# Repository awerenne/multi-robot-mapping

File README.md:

# Multi-robot environment mapping 

The goal of this project was to construct two robots, able to map unknown environments as quickly as possible. The considered environments are exclusively composed of straight black lines on a white background, intersecting each other with right angles. The robots being only allowed to move along those black lines during the exploration phase.

The developed solution follows a master-slave architecture. Each robot (slave) follows a black line while keeping track of the travelled distance. Once an intersection detected, the robot stops and sends an information message to the master. The message contains the type of intersection encountered and the travelled distance since the previous intersection. This information is then used by a program (master), running locally on a computer, in order to update its internal representation of the environment (i.e. map). The next instruction (stop, straight, turn left or right, uturn) for the robot is then computed and send back to the rboto. This procedure is repeated until the environment is entirely explored.

<p align="center">
    &nbsp;&nbsp;&nbsp;
    
</p>

The left-part of the animation above shows a live screen recording of the master constructing the map, corresponding to the robot exploration performed (displayed in the right-part). A video of the complete demonstration can be found [here](https://www.youtube.com/watch?v=w8zaz-Xr6bw&t=6s). The implementation and results are described in the [report](https://awerenne.github.io/files/pp-report.pdf). The different steps of the construction of the robots are documented [here](https://github.com/awerenne/multi-robot-mapping/blob/master/construction/README.md).

## Simulator
Testing the mapping algorithm with the exploration being performed by physical robots would have been time-consuming. Instead, the exploration was simulated on random environments. 

The algorithm of the master is explained in the [report](report/personal-project.pdf)) (pages 8-11). A simulation can be lauched with <code>python main.py</code> in the folder *code/simulator/*. The flag <code>is_simulation</code> needs to be set to true in the config file.

## Robot
The control of the robot was tested with a simple challenge: following a curved line at a constant speed. To this end, a speed and steering controller were developed (described in the [report](report/personal-project.pdf), pages 20-24). The result is shown in the animation below.

The robot was then further augmented to loop through a serie of steps during the exploration phase. The high-level view of the main algorithm (serie of steps) is implemented in the file *code/robot/mapping/mapping.ino*, which is based on low-level features implemented in the files located in the folder *code/robot/NewCOEX/*. The acronym COEX stands for cooperative explorer. 

## Usage
The simulator can be launched as follows:
1. Set the flag <code>is_simulation</code> to True in the config file.
2. Run the command <code>python main.py</code> (in the folder *code/simulator/*).

The physical exploration can be launched as follows:
1. Copy the folder *code/robot/NewCoex* in your Arduino folder, and load it as a library ([how to load a library](https://www.arduino.cc/en/guide/libraries)).
2. Install the library corresponding to the [QTR-X sensors](https://www.pololu.com/docs/0J19/2).
3. Upload the program *code/robot/mapping/mapping.ino* to the micro-controller.
4. Set the flag <code>is_simulation</code> to False in the config file.
5. Check that the ports in the config files are correctly configured with the names of the bluetooth modules.
5. Switch the power of the robots on and calibrate the line sensors.
6. Run the command <code>python main.py</code> (in the folder *code/master/*).

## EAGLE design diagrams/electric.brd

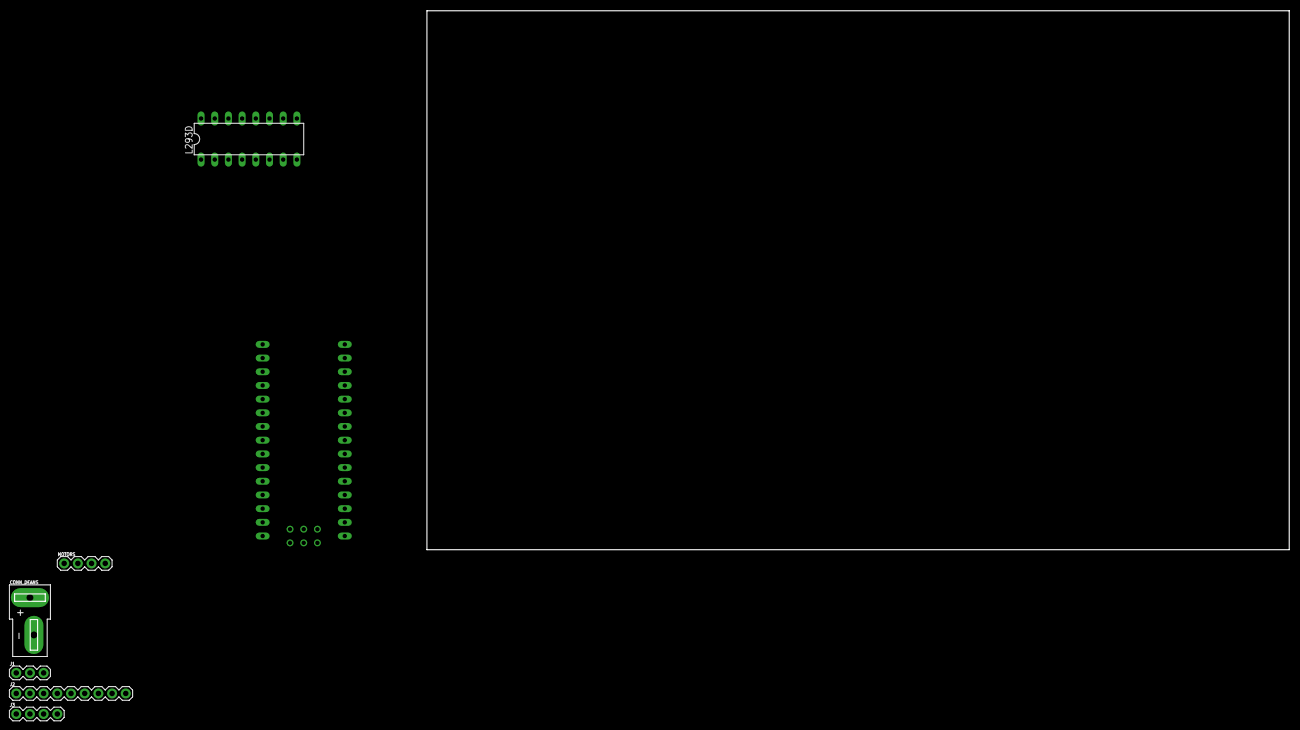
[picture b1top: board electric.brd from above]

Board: 2 copper layers, 7 parts (0 on the bottom side), 7 nets, no tracks yet.

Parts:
CONN_DEANS: DEANS
J1: 1X03
J2: 1X09
J3: 1X04
L293D: L293D; DIL16
MOTORS: 1X04
U$1: NANO

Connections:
GND: CONN_DEANS.-, L293D.4, L293D.5, L293D.12, L293D.13, U$1.GND
GND-LEFT: L293D.6, MOTORS.3
GND-RIGHT: L293D.11, MOTORS.2
V+: CONN_DEANS.+, L293D.8, U$1.RAW
VCC: L293D.16, U$1.5V
VCC-LEFT: L293D.3, MOTORS.4
VCC-RIGHT: L293D.14, MOTORS.1

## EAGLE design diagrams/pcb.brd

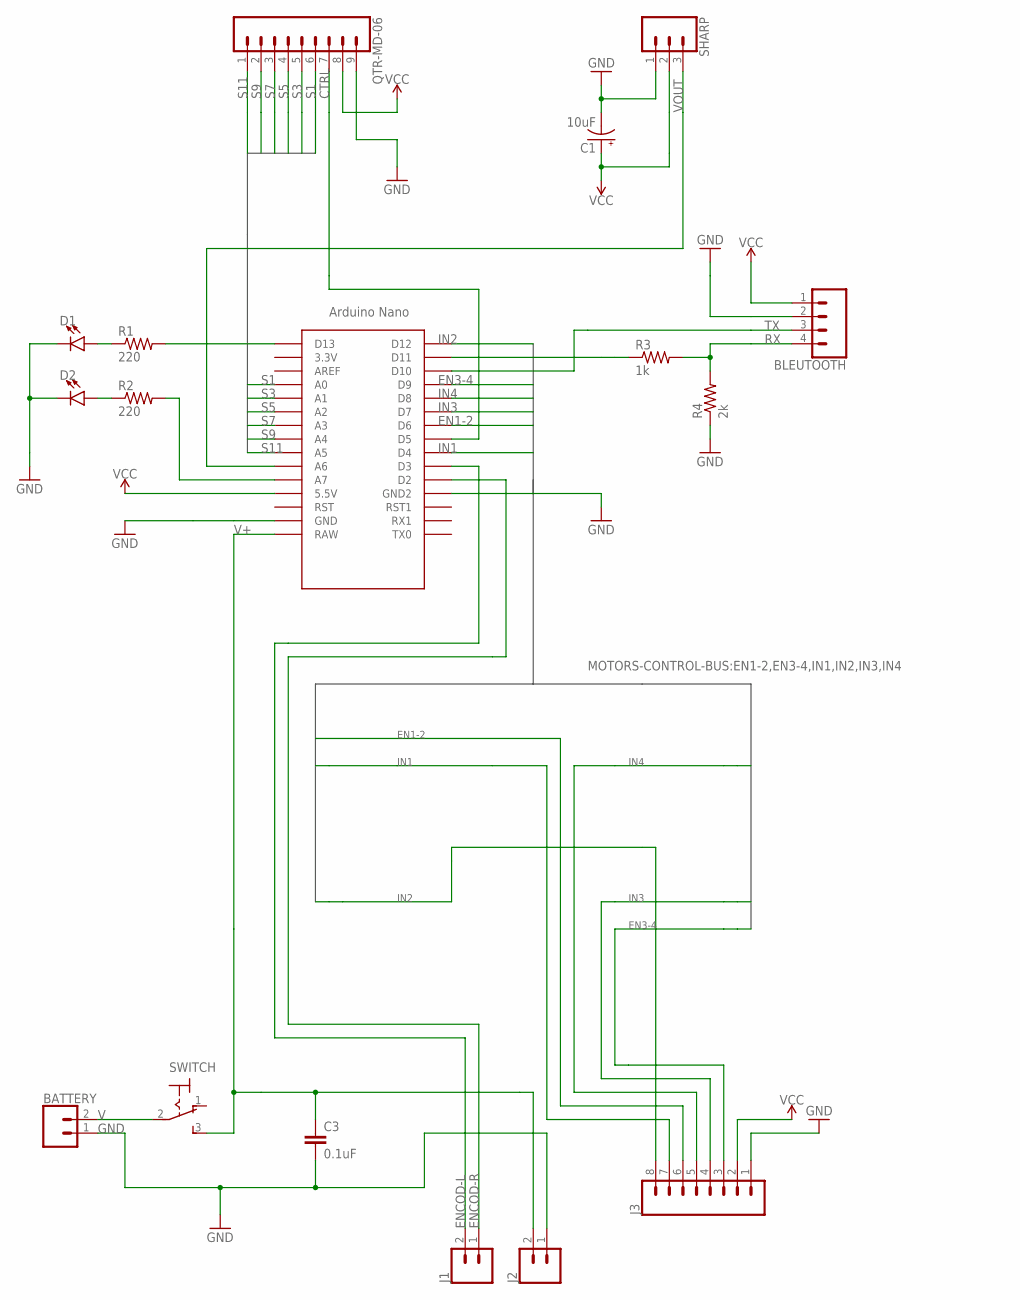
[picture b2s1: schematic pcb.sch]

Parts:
BATTERY: CONN_02; 1X02
BLEUTOOTH: CONN_04; 1X04
C1: 10uF; CPOL-RADIAL-2.5MM-5MM
C3: 0.1uF; CAP-PTH-SMALL-KIT
D1, D2: LED3MM; LED_3MM
J1, J2: CONN_025MM; SCREWTERMINAL-5MM-2
J3: CONN_08"; 1X08
QTR-MD-06: CONN_09; 1X09
R1, R2: 220; 0207/12
R3: 1k; 0207/12
R4: 2k; 0207/12
SHARP: CONN_03; 1X03
SWITCH: 320-916
U$1: NANO

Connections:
CTRL: QTR-MD-06.7, U$1.D5
EN1-2: J3.6, U$1.D6
EN3-4: J3.3, U$1.D9
ENCOD-L: J1.2, U$1.D3
ENCOD-R: J1.1, U$1.D2
GND: BATTERY.1, BLEUTOOTH.2, C1.2 (-), C3.2, D1.K (C), D2.K (C), J2.1, J3.1, QTR-MD-06.9, R4.1, SHARP.1, U$1.GND, U$1.GND1 (GND2)
IN1: J3.7, U$1.D4
IN2: J3.8, U$1.D12
IN3: J3.4, U$1.D7
IN4: J3.5, U$1.D8
unnamed: R2.2, U$1.A7
unnamed: R1.2, U$1.D13
unnamed: D1.A, R1.1
unnamed: D2.A, R2.1
unnamed: R3.1, U$1.D11
RX: BLEUTOOTH.4, R3.2, R4.2
S1: QTR-MD-06.6, U$1.A0
S3: QTR-MD-06.5, U$1.A1
S5: QTR-MD-06.4, U$1.A2
S7: QTR-MD-06.3, U$1.A3
S9: QTR-MD-06.2, U$1.A4
S11: QTR-MD-06.1, U$1.A5
TX: BLEUTOOTH.3, U$1.D10
V: BATTERY.2, SWITCH.2
V+: C3.1, J2.2, SWITCH.3 (S), U$1.RAW
VCC: BLEUTOOTH.1, C1.1 (+), J3.2, QTR-MD-06.8, SHARP.2, U$1.5V (5.5V)
VOUT: SHARP.3, U$1.A6

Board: 2 copper layers, 17 parts (0 on the bottom side), 27 nets, no tracks yet.

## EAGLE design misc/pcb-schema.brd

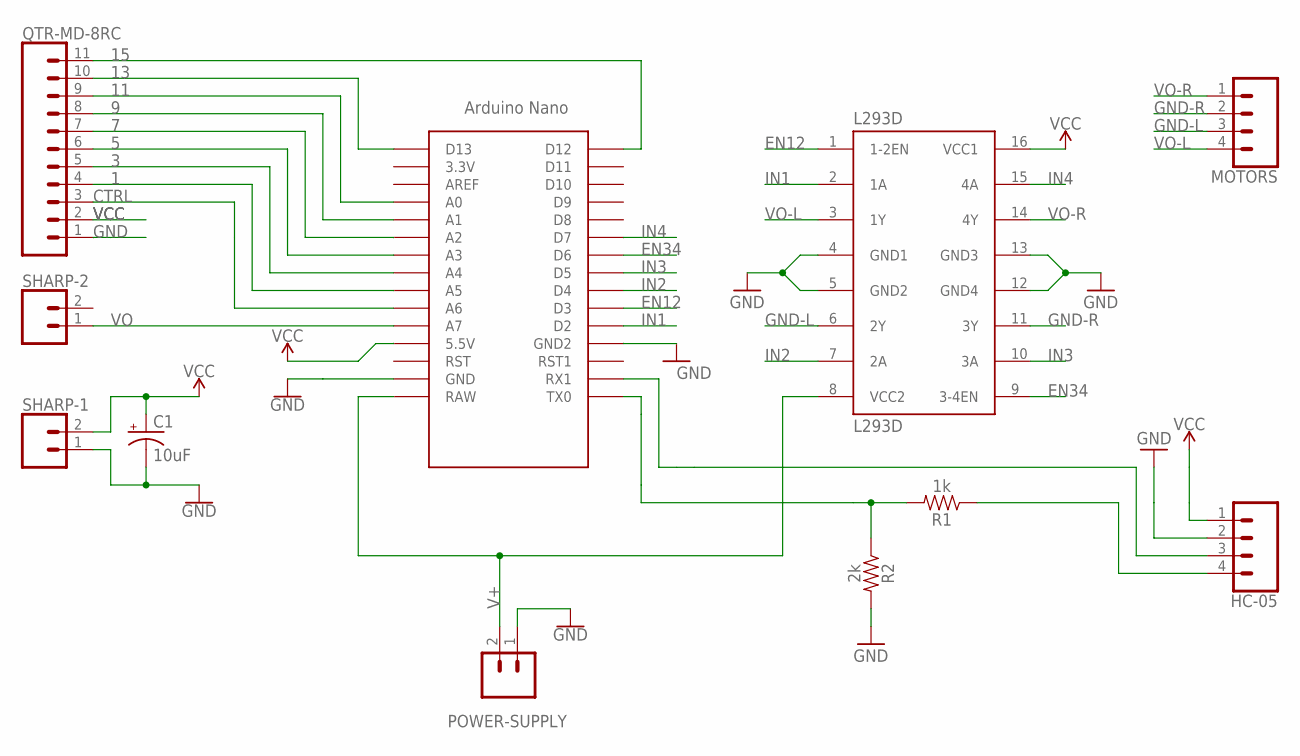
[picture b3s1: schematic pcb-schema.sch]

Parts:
C1: 10uF; CPOL-RADIAL-2.5MM-5MM
HC-05: CONN_04; 1X04
L293D: L293D; DIL16
MOTORS: CONN_04; 1X04
POWER-SUPPLY: CONN_025MM; SCREWTERMINAL-5MM-2
QTR-MD-8RC: CONN_11; 1X11
R1: 1k; AXIAL-0.3
R2: 2k; AXIAL-0.3
SHARP-1, SHARP-2: CONN_025MM; SCREWTERMINAL-5MM-2
U$1: NANO

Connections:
1: QTR-MD-8RC.4, U$1.A5
3: QTR-MD-8RC.5, U$1.A4
5: QTR-MD-8RC.6, U$1.A3
7: QTR-MD-8RC.7, U$1.A2
9: QTR-MD-8RC.8, U$1.A1
11: QTR-MD-8RC.9, U$1.A0
13: QTR-MD-8RC.10, U$1.D13
15: QTR-MD-8RC.11, U$1.D12
CTRL: QTR-MD-8RC.3, U$1.A6
EN12: L293D.1 (1-2EN), U$1.D3
EN34: L293D.9 (3-4EN), U$1.D6
GND: C1.2 (-), HC-05.2, L293D.4 (GND1), L293D.5 (GND2), POWER-SUPPLY.1, QTR-MD-8RC.1, R2.P$2 (2), SHARP-1.1, U$1.GND, U$1.GND1 (GND2)
GND-L: L293D.6 (2Y), MOTORS.3
GND-R: L293D.11 (3Y), MOTORS.2
IN1: L293D.2 (1A), U$1.D2
IN2: L293D.7 (2A), U$1.D4
IN3: L293D.10 (3A), U$1.D5
IN4: L293D.15 (4A), U$1.D7
unnamed: L293D.12 (GND4), L293D.13 (GND3)
unnamed: HC-05.3, U$1.RX1
unnamed: HC-05.4, R1.P$1 (1)
unnamed: R1.P$2 (2), R2.P$1 (1), U$1.TX0
V+: L293D.8 (VCC2), POWER-SUPPLY.2, U$1.RAW
VCC: C1.1 (+), HC-05.1, L293D.16 (VCC1), QTR-MD-8RC.2, SHARP-1.2, U$1.5V (5.5V)
VO: SHARP-2.1, U$1.A7
VO-L: L293D.3 (1Y), MOTORS.4
VO-R: L293D.14 (4Y), MOTORS.1

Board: 2 copper layers, 11 parts (0 on the bottom side), 27 nets, no tracks yet.

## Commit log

2018-10-08 Initial structure of modules
    Simulator, Master, Worker
2018-10-30 Tests & bugs
    Adding of hardware tests. FIx bugs in simulator.
2018-11-03 Naive solution
2018-11-26 Hardware tests & fix merge maps
2019-01-07 Test 1-9 & RobotInterface update
2019-01-09 Test distance estimation & GUI
2019-01-10 Refactor structure of Master
    & Redo Map class
2019-01-11 Finish Map & GUI class
    + main script in Master
2019-01-11 Test A* star
2019-01-14 GUI with buttons
    + Automatic calibration
    + Mutually inclusive classes bug fixed
    + Intersection detection fixed
2019-01-14 Refactored robot interface (passed test 9!)
2019-01-18 Multi-threaded architecture
    + finish test shortest path test
    + clean utils
2019-01-18 Improve distance approximation (include oneinch)
    + more robust intersection detection
2019-01-21 Inheritance Master & Improved Graph structure
    + refactoring of map, graph
2019-01-26 Master without bug (simulation & real world are working)
2019-02-03 New GUI design
2019-02-04 Demos
2019-02-19 Drawings playgrounds
2019-02-20 Refactoring tests
    Component tests done. Control tests in progress. Adding of Coex class (high level features of the robot)
2019-02-20 Coex class (high level features)
2019-02-21 Speed control and forward control (tests passed)
    PID with anti-windup
2019-02-22 Forward and turn control at constant speed
    Advanced tests qtr sensor, turn 90-180, frequencystate class, PID with init problem fixed
2019-02-24 Acceleration with smooth option
2019-02-24 Control tests done
2019-02-25 Automatic calib test (in progress) & back and forth
2019-02-25 Rotation depending on target angle + model
2019-02-26 Add control functions to coex
2019-02-26 Updated coex, Manual with GUI, distance test
2019-02-26 Decaying speed for rotation alignement (simulation)
2019-02-28 Anomalies class
2019-03-01 Latex slides robot & intersection test
2019-03-02 General structure slides + maths
2019-03-02 Further tuning of control & passing of aligning test
2019-03-03 Intersection detection + aligning
2019-03-04 Include maths in latex
2019-03-05 Electric diagram + new tests
2019-03-09 Draw maze with cycles
2019-03-09 Update schematic
2019-03-10 Update figs for slides
2019-03-10 Update Latex + Pid shaded plot + Sinus test plot
2019-03-11 Slides with content - improved readability plots
2019-03-12 Perturbation test & PCB
2019-03-13 Review slides & cleaner plots
2019-03-16 Update slides
2019-03-16 Zeta function + finish plots distance/perturbation
2019-03-17 Finished first version of slides
2019-03-17 Intersection detection fixed
2019-03-17 Maze solving in COEX
2019-03-17 Maze solving linked to master
    issue: bug for front detection
2019-03-18 Maze mapping without bugs
2019-03-18 Finished demo
2019-03-20 Initial PCB sketch
2019-06-19 Faster fluent motion
2019-06-25 Template grid diagram
2019-06-25 Random map generation
2019-06-27 SImulator multi robot run
2019-08-28 Clean & Refactor
2019-08-29 Test gif
2019-08-29 Center gif
2019-08-29 Title fix
2019-08-29 Fix readme
2019-08-29 Fix readme gif
2019-09-04 Clean readme with animations & debug demo one-robot
2019-09-04 Photos construction steps
2019-09-04 Pictures in readme
2019-09-16 Fix bluetooth bug when using two robots & update readme &
2019-09-16 Correction typo readme
2019-09-17 Correction typos readme & report
2019-09-22 Final update
2019-09-23 Add extra step installation - pololu install library
2019-10-01 Improve syntax readme
2019-10-04 Add connectivity diagram link
2019-10-04 Add .
2020-01-17 Update documentation
2020-01-17 Add construction steps to documentation

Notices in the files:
parts and their libraries:
SparkFun-Connectors: Licensing: Creative Commons ShareAlike 4.0 International - https://creativecommons.org/licenses/by-sa/4.0
